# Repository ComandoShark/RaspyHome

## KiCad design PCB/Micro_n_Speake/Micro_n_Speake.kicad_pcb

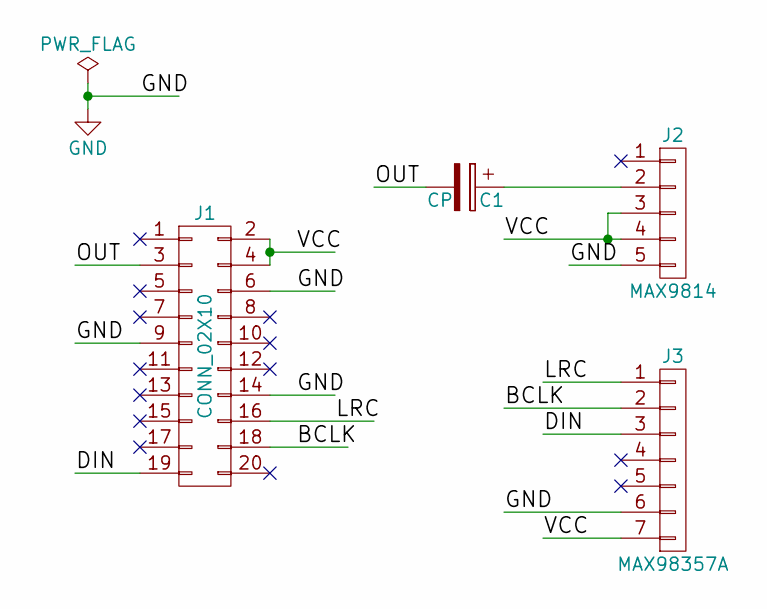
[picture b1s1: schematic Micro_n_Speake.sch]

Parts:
C1: CP; CP_Elec_8x6.5
J1: CONN_02X10; Pin_Header_Straight_2x10_Pitch2.54mm
J2: MAX9814; Pin_Header_Straight_1x05_Pitch2.54mm
J3: MAX98357A; Pin_Header_Straight_1x07_Pitch2.54mm

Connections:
/BCLK: J1.18, J3.2
/DIN: J1.19, J3.3
/LRC: J1.16, J3.1
/OUT: C1.2, J1.3
/VCC: J1.2, J1.4, J2.3, J2.4, J3.7
GND: J1.6, J1.9, J1.14, J2.5, J3.6
unnamed: C1.1, J2.2

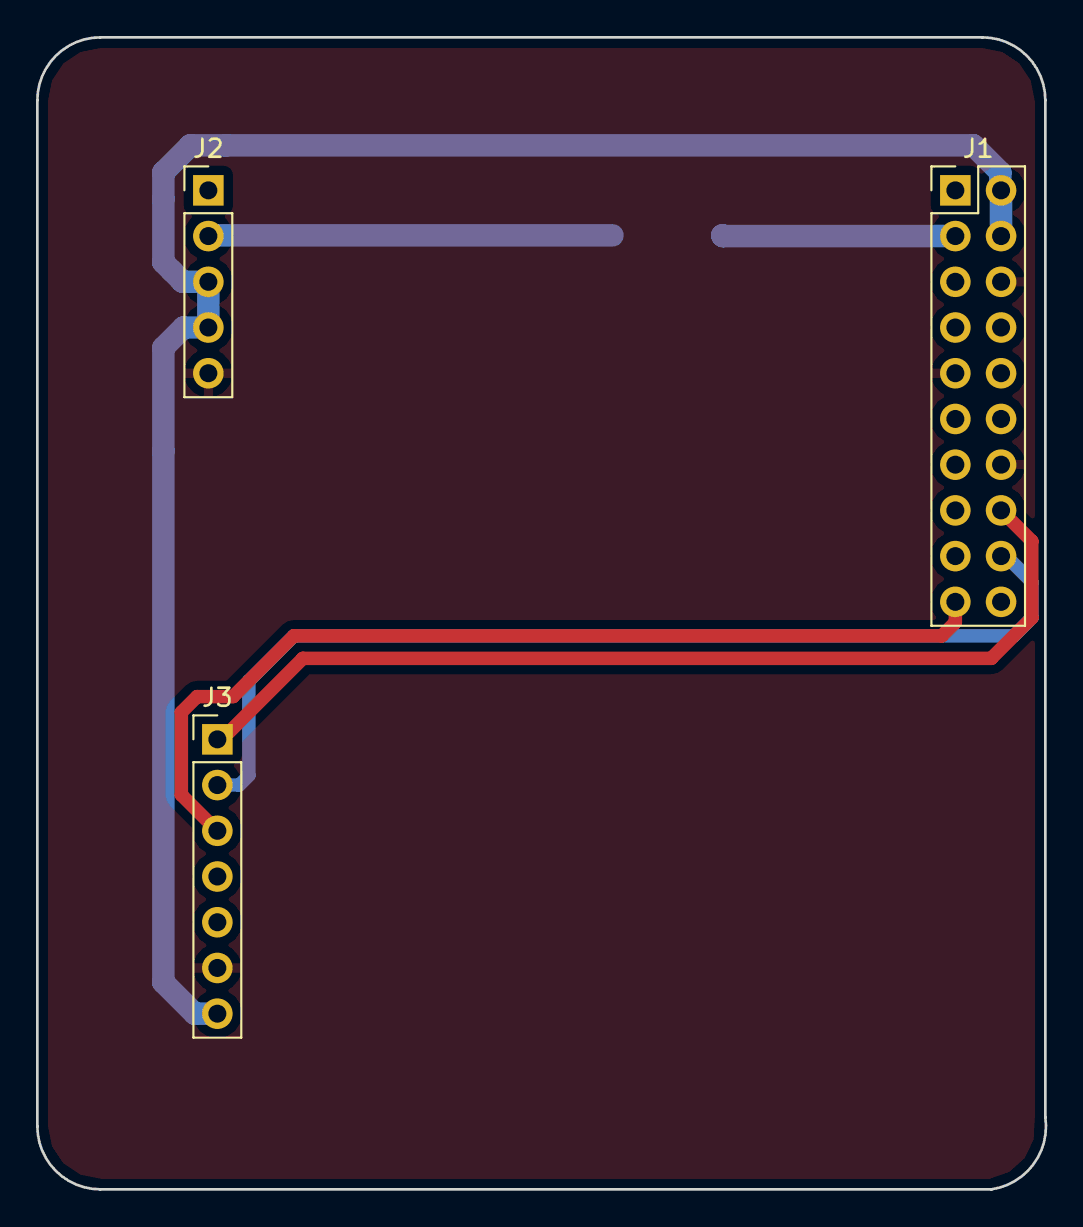
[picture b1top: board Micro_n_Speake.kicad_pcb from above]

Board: 2 copper layers, 56.0 x 64.0 mm, 4 parts (1 on the bottom side), 7 nets.

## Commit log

2017-04-05 :octocat: Added .gitattributes & .gitignore files
2017-04-05 base de donnée
2017-04-05 base de données
2017-04-05 Code
2017-04-06 Next+Ultra
2017-04-06 Code 11:47
2017-04-06 new method
2017-04-07 New code
2017-04-07 test
2017-04-07 Interface finale
2017-04-10 poster
2017-04-11 new poster
2017-04-26 commit 17:28
2017-04-28 texttospeech
2017-05-12 new one
2017-05-19 Jeudi 18.05.17
    maj SpeechNSynthetize
    maj Server
    create SenseHAT
    create PiFace2
    StreamSocket client
2017-05-19 vendredi 18.05.17
    maj server et client
2017-05-26 Vendredi 26 mai 2017 17:21
2017-06-02 vendredi 2 juin2017
2017-06-07 dfgdfg
2017-06-08 Jeudi 08 06 2017
    Application finie
    Commentaire presque tous rédigé
2017-06-09 Vendredi 09.06.2017
    Codes commented
2017-06-09 Vendredi 09.06.2017
    Last before W-E
2017-06-12 Final push
2017-06-12 Final program
    Monday 12 juny 2017
2017-06-12 Image added
2017-06-12 Remove zip
2017-06-13 Add image
